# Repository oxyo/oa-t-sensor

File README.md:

## Open Automation wireless temperature sensor board   

Used [Ciseco XRF wireless RF radio UART serial data module][] with [temperature sensor firmware loaded](http://openmicros.org/index.php/articles/87-llap-devices-commands-and-instructions/122-xrf-firmware-temp). It sends temerature values in 1 min. intervals to Open Automation Center. To extend sensor lifetime and temperature range LiFePO4 Lithium Ion Cylindrical Cell used.

This simple device can measure air temperature in range -30..+60 up to 0.5% precision. 
  
Schematics and board files provided. Ciseco thermistor firmware can be downloaded from [here](https://github.com/CisecoPlc/XRF-Firmware-downloads).
  
For more information please visit [openautomation.center](http://openautomation.center)

Licensed under [WTFPL license terms](http://www.wtfpl.net/)

[Ciseco XRF wireless RF radio UART serial data module]: http://shop.ciseco.co.uk/xrf-wireless-rf-radio-uart-serial-data-module-xbee-shaped/

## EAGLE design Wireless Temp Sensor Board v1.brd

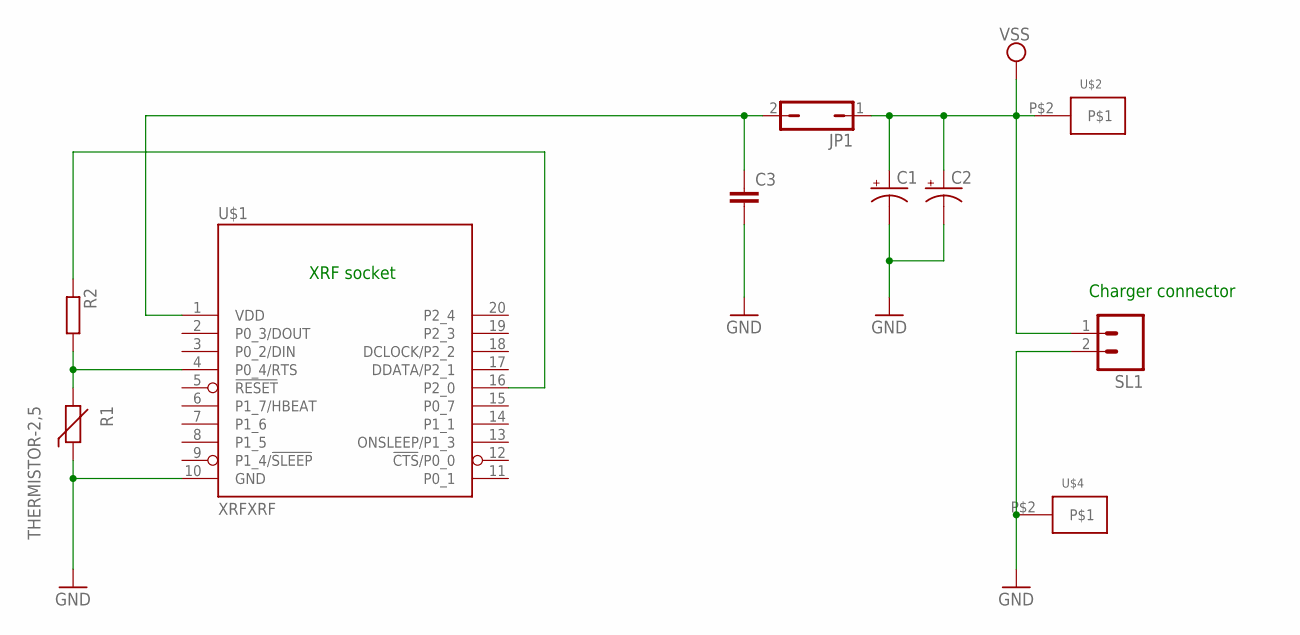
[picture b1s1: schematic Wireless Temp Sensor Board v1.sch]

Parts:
C1: CPOL-USE5-10.5; E5-10,5
C2: CPOL-USE3.5-8; E3,5-8
C3: C-EU025-025X050; C025-025X050
JP1: JP1Q; JP1
R1: THERMISTOR-2,5; RS-2,5
R2: R-EU_0207/12; 0207/12
SL1: M02; 02P
U$1: XRFXRF; XRF
U$2, U$4: HORSESHOEDPAD; HORSESHOEPAD

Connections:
GND: C1.-, C2.-, C3.2, R1.1, SL1.2, U$1.10 (GND), U$4.P$2
unnamed: R2.1, U$1.16 (P2_0)
unnamed: R1.2, R2.2, U$1.4 (P0_4/RTS)
unnamed: C3.1, JP1.2, U$1.1 (VDD)
VSS: C1.+, C2.+, JP1.1, SL1.1, U$2.P$2

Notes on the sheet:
Charger connector
XRF socket

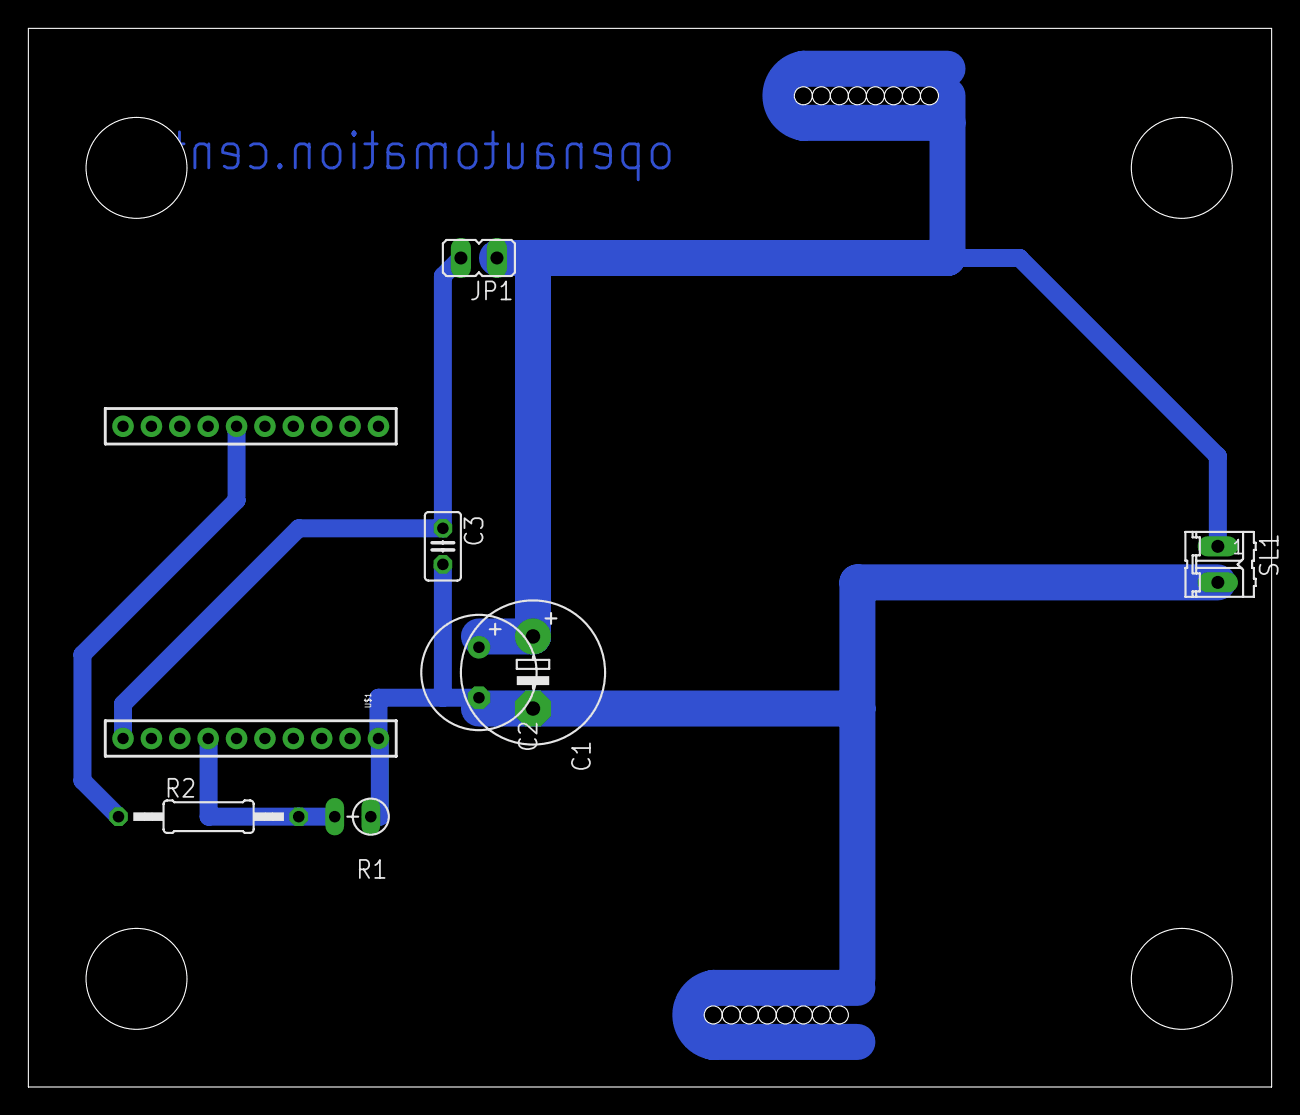
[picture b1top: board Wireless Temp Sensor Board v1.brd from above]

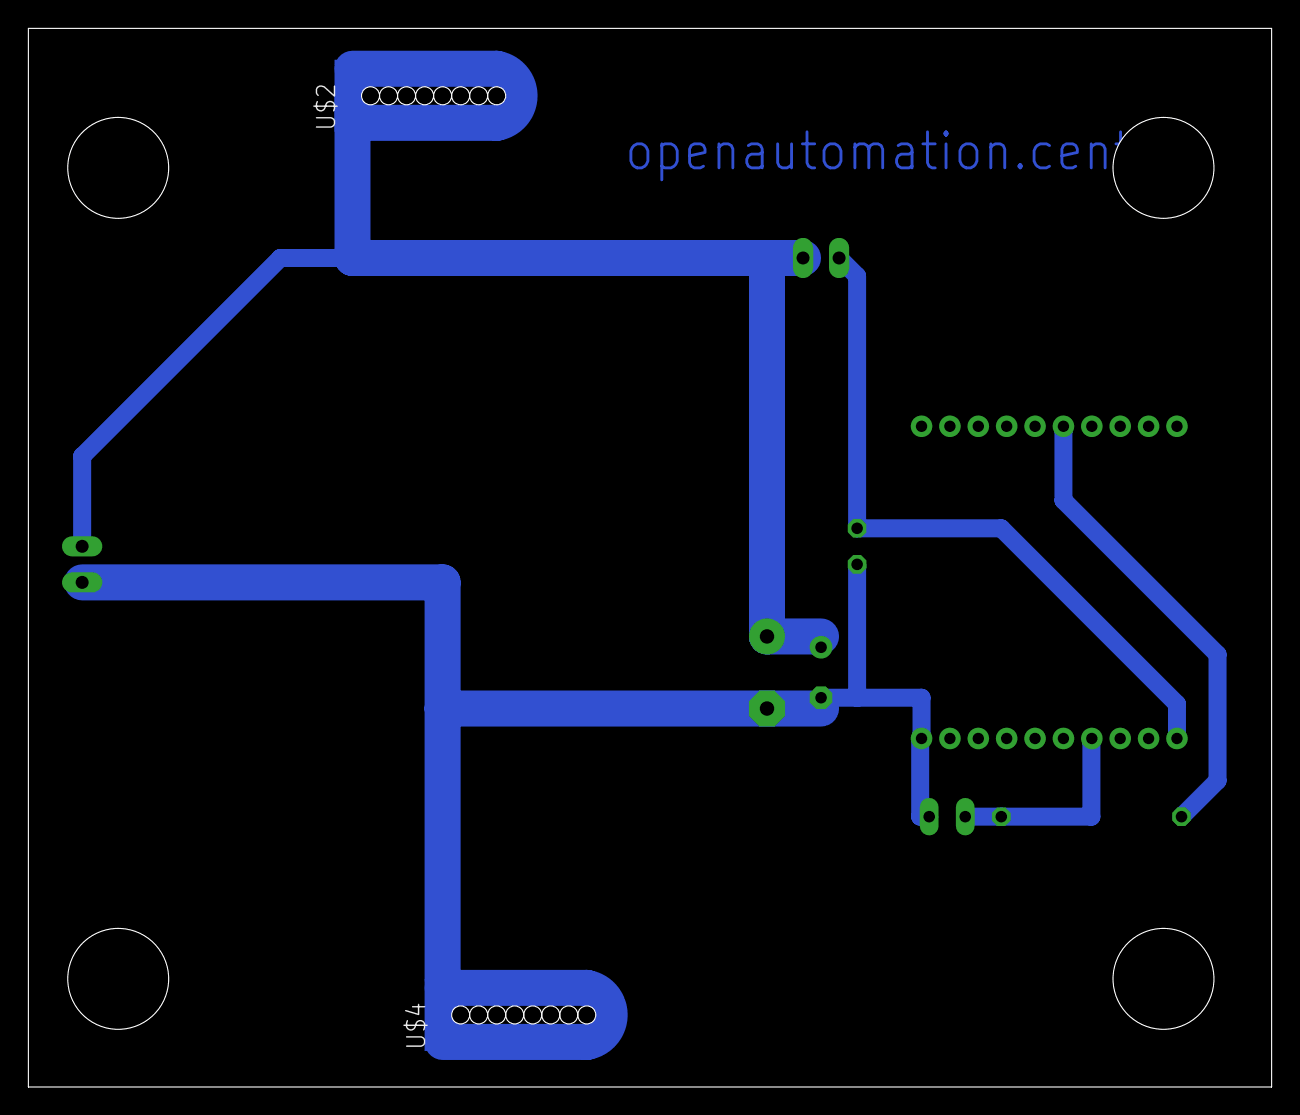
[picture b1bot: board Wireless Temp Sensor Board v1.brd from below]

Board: 2 copper layers, 87.6 x 74.6 mm, 10 parts (2 on the bottom side), 5 nets.

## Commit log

2015-03-30 Update LICENSE
